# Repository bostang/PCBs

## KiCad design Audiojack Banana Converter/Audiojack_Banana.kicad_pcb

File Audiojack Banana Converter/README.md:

# Audiojack-Banana Converter

Converter audijoack 3.5mm <-> Banana Connector untuk keperluan pengujian _amplifier_ dengan input audio untuk tugas besar EL2205 Praktikum Elektronika 2024.

# Skematik

# Tampilan

## Tampak Atas

## Tampak Bawah

## Bird-view

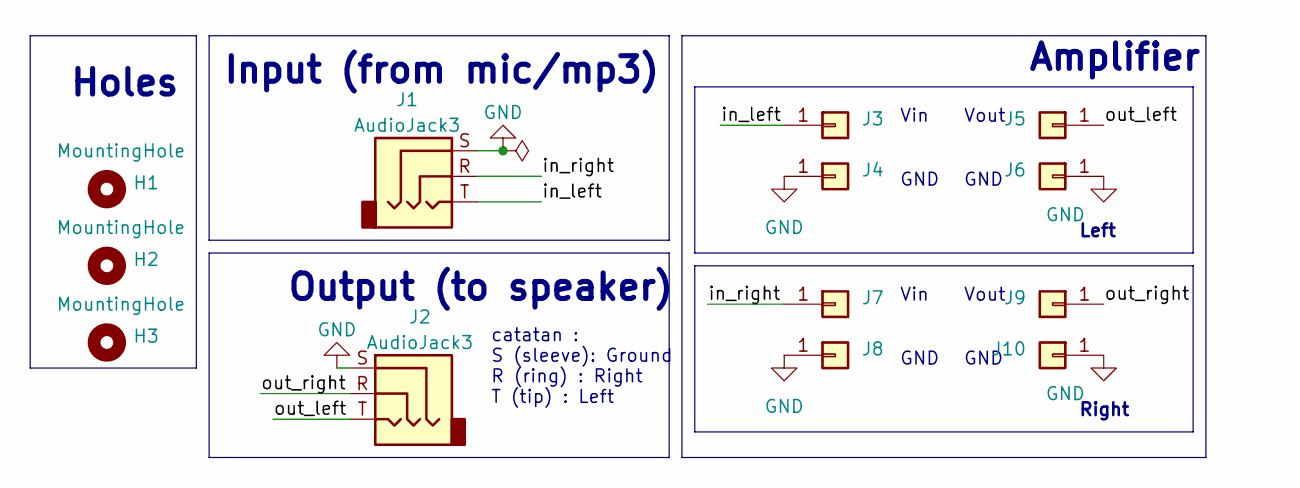
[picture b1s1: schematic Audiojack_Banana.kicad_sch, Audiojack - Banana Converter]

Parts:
H1, H2, H3: MountingHole; MountingHole_3.2mm_M3
J1, J2: AudioJack3; Jack_3.5mm_CUI_SJ-3523-SMT_Horizontal
J3, J4, J5, J6, J7, J8, J9, J10: Conn_01x01; Banana_Jack_1Pin

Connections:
/in_left: J1.T, J3.1
/in_right: J1.R, J7.1
/out_left: J2.T, J5.1
/out_right: J2.R, J9.1
GND: J1.S, J2.S, J4.1, J6.1, J8.1, J10.1

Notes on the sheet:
Amplifier
Vin
Vout
catatan : S (sleeve): Ground R (ring) : Right T (tip) : Left
Input (from mic/mp3)
GND
Left
Output (to speaker)
Right
Holes

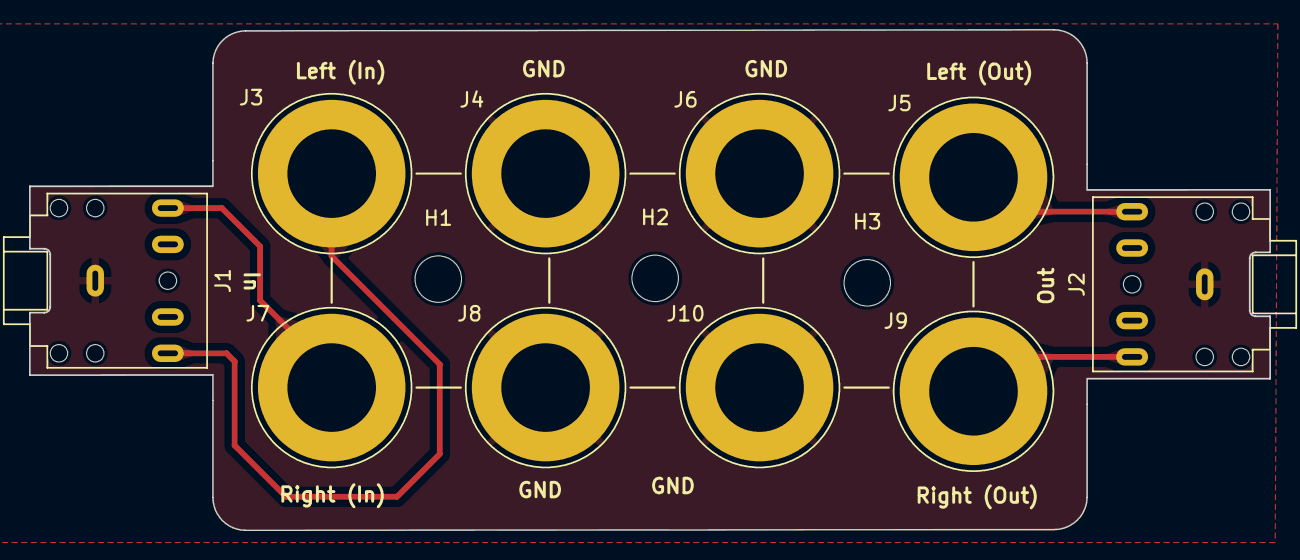
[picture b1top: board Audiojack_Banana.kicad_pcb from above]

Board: 2 copper layers, 85.4 x 34.5 mm, 13 parts (0 on the bottom side), 5 nets.

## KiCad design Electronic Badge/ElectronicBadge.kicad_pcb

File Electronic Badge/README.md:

# Electronic Badge

Lencana Elektronik yang berisi sebuah rangkaian sederhana : transistor sebagai switch sebagai tanda apresiasi bagi praktikan EL2205 Praktikum Elektronika 2024.

# Skematik

# Tampilan

## Tampak Atas

## Tampak Bawah

## Bird-view

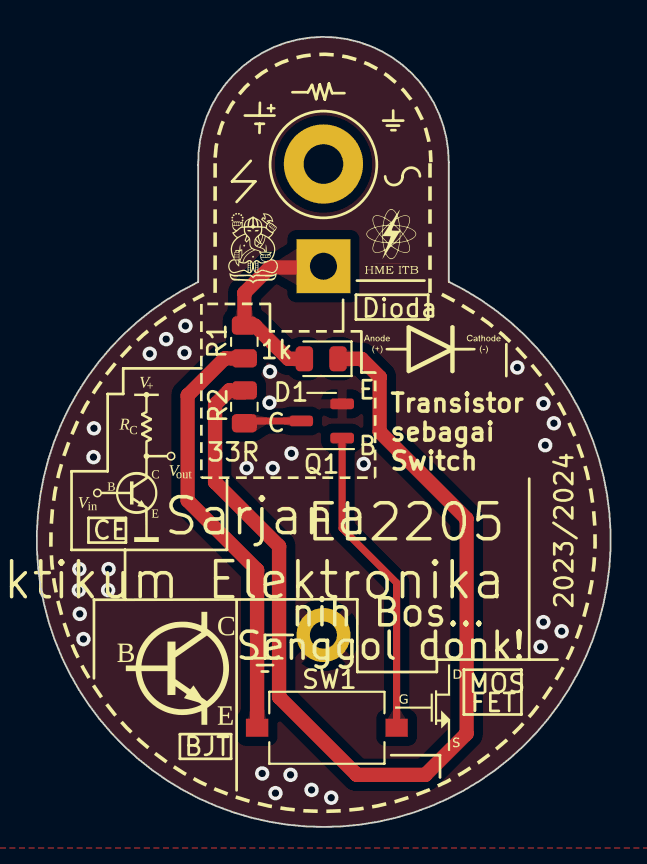
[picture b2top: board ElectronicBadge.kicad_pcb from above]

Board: 2 copper layers, 31.9 x 43.9 mm, 7 parts (1 on the bottom side), 6 nets.

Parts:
BT1: 3V; BatteryHolder_Keystone_107_1x23mm
D1: LED; LED_0805_2012Metric
H1: MountingHole; MountingHole_2.2mm_M2_Pad
Q1: NPN; SOT-23-3
R1: 1k; R_0805_2012Metric
R2: 33; R_0805_2012Metric
SW1: SW_SPST; SW_Tactile_SPST_NO_Straight_CK_PTS636Sx25SMTRLFS

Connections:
GND: BT1.2 (-), Q1.2 (E)
unnamed: D1.1 (K), R2.1
unnamed: Q1.1 (B), SW1.2 (B)
unnamed: Q1.3 (C), R2.2
unnamed: R1.2, SW1.1 (A)
VCC: BT1.1 (+), D1.2 (A), R1.1

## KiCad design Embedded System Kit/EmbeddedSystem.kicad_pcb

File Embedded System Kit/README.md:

# Embedded System Kit

Programmable ESP-32 development kit untuk tugas-tugas projek mata kuliah EL4121 Perancangan Sistem Embedded.

# Skematik

# Tampilan

## Tampak Atas

## Tampak Bawah

## Bird-view

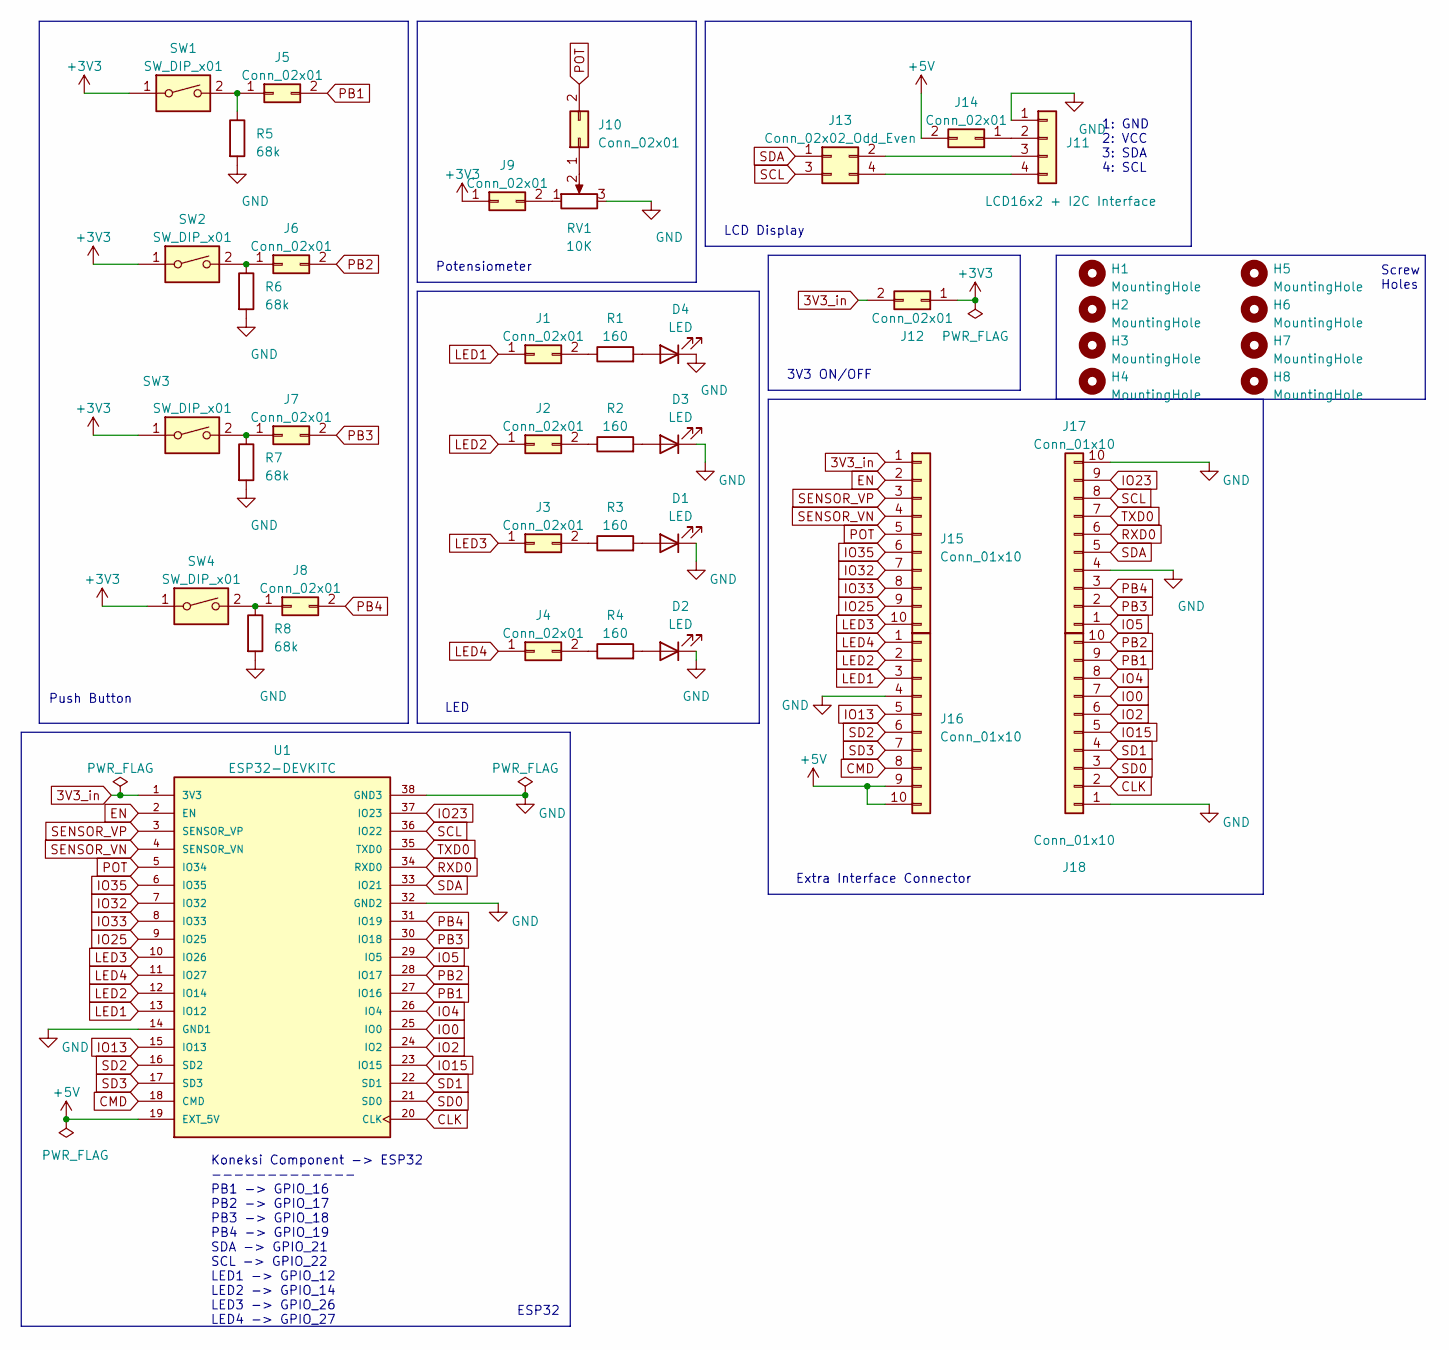
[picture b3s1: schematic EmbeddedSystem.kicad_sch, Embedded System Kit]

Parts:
D1, D2, D3, D4: LED; LED_0805_2012Metric
H1, H2, H3, H4, H5, H6, H7, H8: MountingHole; MountingHole_2.5mm
J1, J2, J3, J4, J5, J6, J7, J8, J9, J10, J12, J14: Conn_02x01; PinHeader_1x02_P2.54mm_Vertical
J11: LCD16x2 + I2C Interface; PinHeader_1x04_P2.54mm_Vertical
J13: Conn_02x02_Odd_Even; PinHeader_2x02_P2.54mm_Vertical
J15, J16, J17, J18: Conn_01x10; PinHeader_1x10_P2.54mm_Vertical
R1, R2, R3, R4: 160; R_0805_2012Metric
R5, R6, R7, R8: 68k; R_0805_2012Metric
RV1: 10K; Potentiometer_Alpha_RD901F-40-00D_Single_Vertical
SW1, SW2, SW3, SW4: SW_DIP_x01; SW_SPST_TL3342
U1: ESP32-DEVKITC; MODULE_ESP32-DEVKITC; PARTREV N/A

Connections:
3V3_in: J12.2, J15.1, U1.1 (3V3)
+3V3: J9.1, J12.1, SW1.1, SW2.1, SW3.1, SW4.1
+5V: J14.2, J16.9, J16.10, U1.19 (EXT_5V)
CLK: J18.2, U1.20 (CLK)
CMD: J16.8, U1.18 (CMD)
EN: J15.2, U1.2 (EN)
GND: D1.1 (K), D2.1 (K), D3.1 (K), D4.1 (K), J11.1, J16.4, J17.4, J17.10, J18.1, R5.2, R6.2, R7.2, R8.2, RV1.3, U1.14 (GND1), U1.32 (GND2), U1.38 (GND3)
IO0: J18.7, U1.25 (IO0)
IO2: J18.6, U1.24 (IO2)
IO4: J18.8, U1.26 (IO4)
IO5: J17.1, U1.29 (IO5)
IO13: J16.5, U1.15 (IO13)
IO15: J18.5, U1.23 (IO15)
IO23: J17.9, U1.37 (IO23)
IO25: J15.9, U1.9 (IO25)
IO32: J15.7, U1.7 (IO32)
IO33: J15.8, U1.8 (IO33)
IO35: J15.6, U1.6 (IO35)
LED1: J1.1, J16.3, U1.13 (IO12)
LED2: J2.1, J16.2, U1.12 (IO14)
LED3: J3.1, J15.10, U1.10 (IO26)
LED4: J4.1, J16.1, U1.11 (IO27)
unnamed: D1.2 (A), R3.2
unnamed: D2.2 (A), R4.2
unnamed: D3.2 (A), R2.2
unnamed: D4.2 (A), R1.2
unnamed: J1.2, R1.1
unnamed: J2.2, R2.1
unnamed: J3.2, R3.1
unnamed: J4.2, R4.1
unnamed: J5.1, R5.1, SW1.2
unnamed: J6.1, R6.1, SW2.2
unnamed: J7.1, R7.1, SW3.2
unnamed: J8.1, R8.1, SW4.2
unnamed: J9.2, RV1.1
unnamed: J10.1, RV1.2
unnamed: J11.2, J14.1
unnamed: J11.3, J13.2
unnamed: J11.4, J13.4
PB1: J5.2, J18.9, U1.27 (IO16)
PB2: J6.2, J18.10, U1.28 (IO17)
PB3: J7.2, J17.2, U1.30 (IO18)
PB4: J8.2, J17.3, U1.31 (IO19)
POT: J10.2, J15.5, U1.5 (IO34)
RXD0: J17.6, U1.34 (RXD0)
SCL: J13.3, J17.8, U1.36 (IO22)
SD0: J18.3, U1.21 (SD0)
SD1: J18.4, U1.22 (SD1)
SD2: J16.6, U1.16 (SD2)
SD3: J16.7, U1.17 (SD3)
SDA: J13.1, J17.5, U1.33 (IO21)
SENSOR_VN: J15.4, U1.4 (SENSOR_VN)
SENSOR_VP: J15.3, U1.3 (SENSOR_VP)
TXD0: J17.7, U1.35 (TXD0)

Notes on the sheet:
Extra Interface Connector
1: GND 2: VCC 3: SDA 4: SCL
ESP32
Potensiometer
LED
Screw Holes
Push Button
Koneksi Component -> ESP32 ------------- PB1 -> GPIO_16 PB2 -> GPIO_17 PB3 -> GPIO_18 PB4 -> GPIO_19 SDA -> GPIO_21 SCL -> GPIO_22 LED1 -> GPIO_12 LED2 -> GPIO_14 LED3 -> GPIO_26 LED4 -> GPIO_27
LCD Display
3V3 ON/OFF

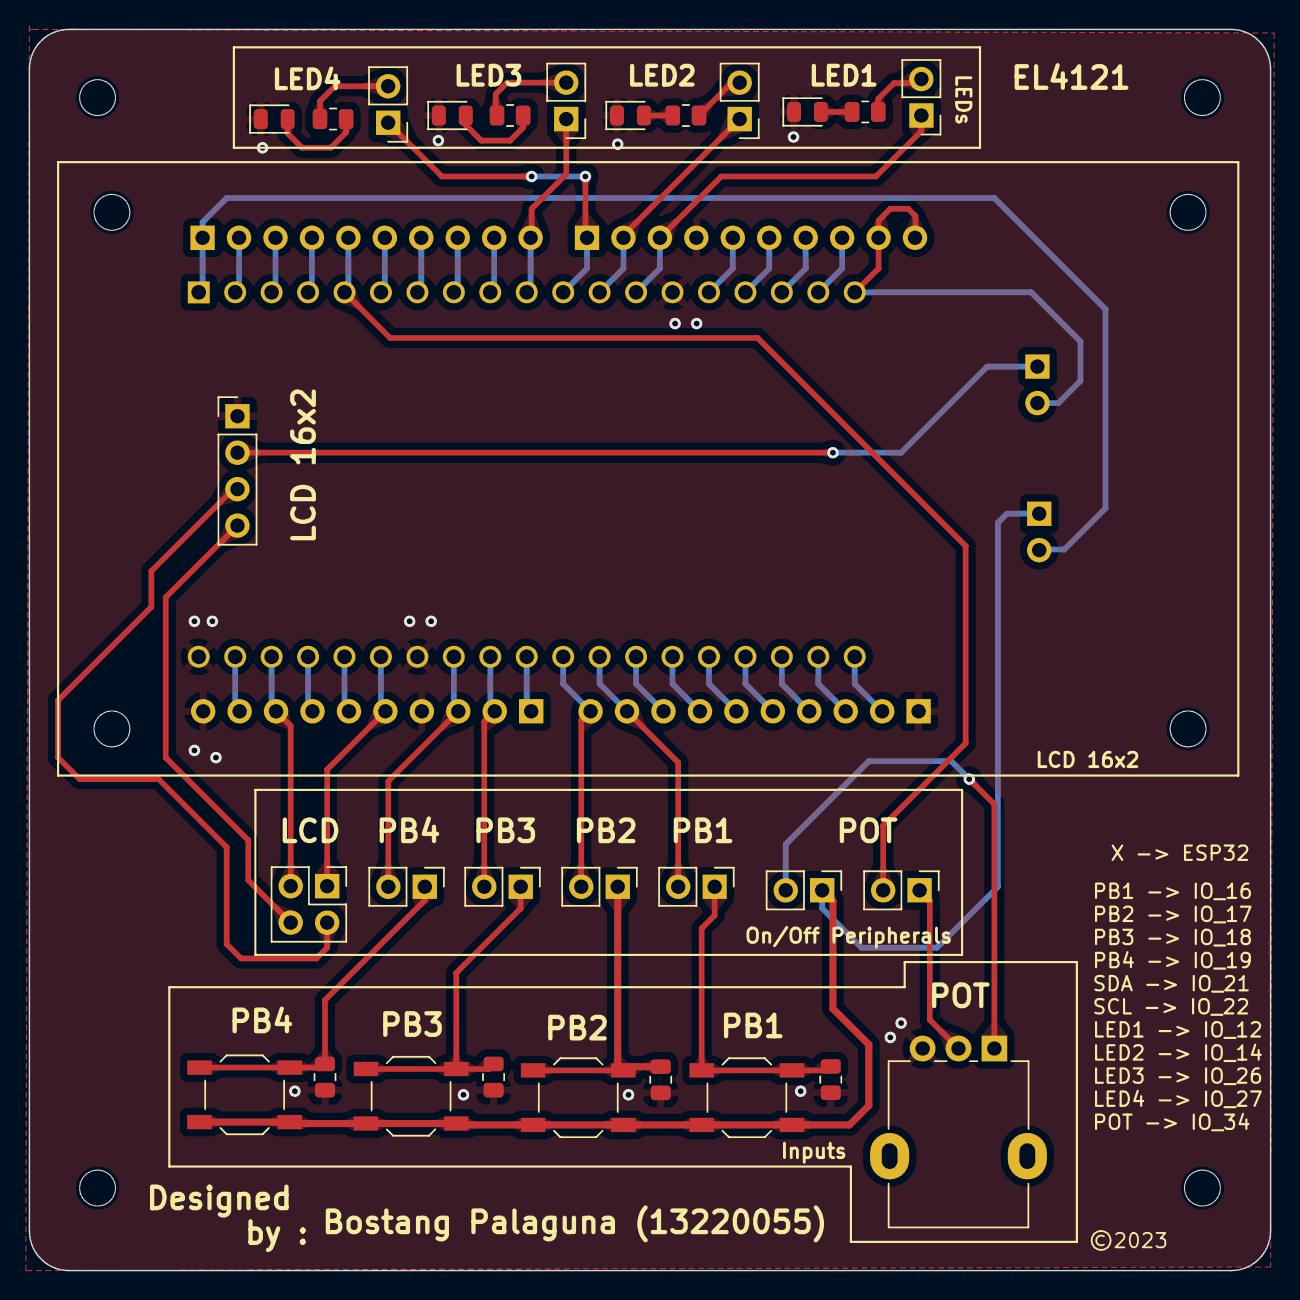
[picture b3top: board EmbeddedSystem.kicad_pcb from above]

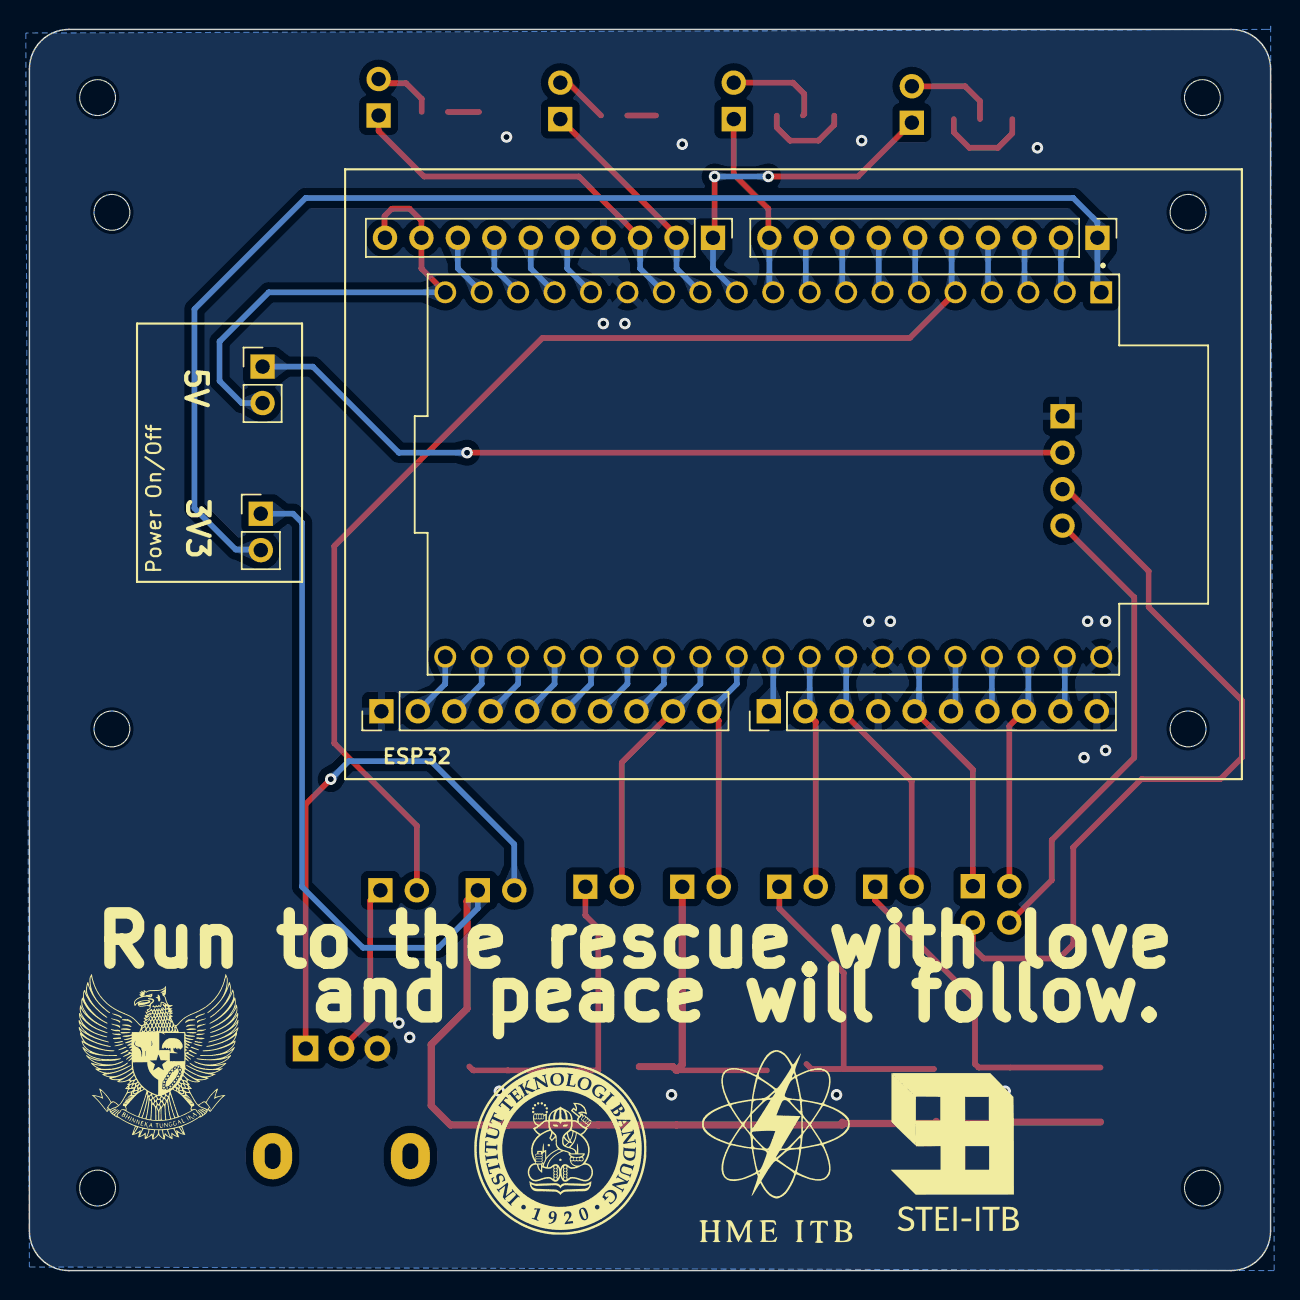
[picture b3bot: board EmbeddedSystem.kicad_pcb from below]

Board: 2 copper layers, 86.5 x 86.5 mm, 44 parts (7 on the bottom side), 54 nets.

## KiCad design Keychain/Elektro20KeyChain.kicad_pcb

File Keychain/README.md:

# Electronic KeyChain

Sebuah gantungan kunci dengan rangkaian empat LED sebagai tanda solidaritas Teknik Elektro ITB angkatan 2020.

# Skematik

# Tampilan

## Tampak Atas

## Tampak Bawah

## Bird-view

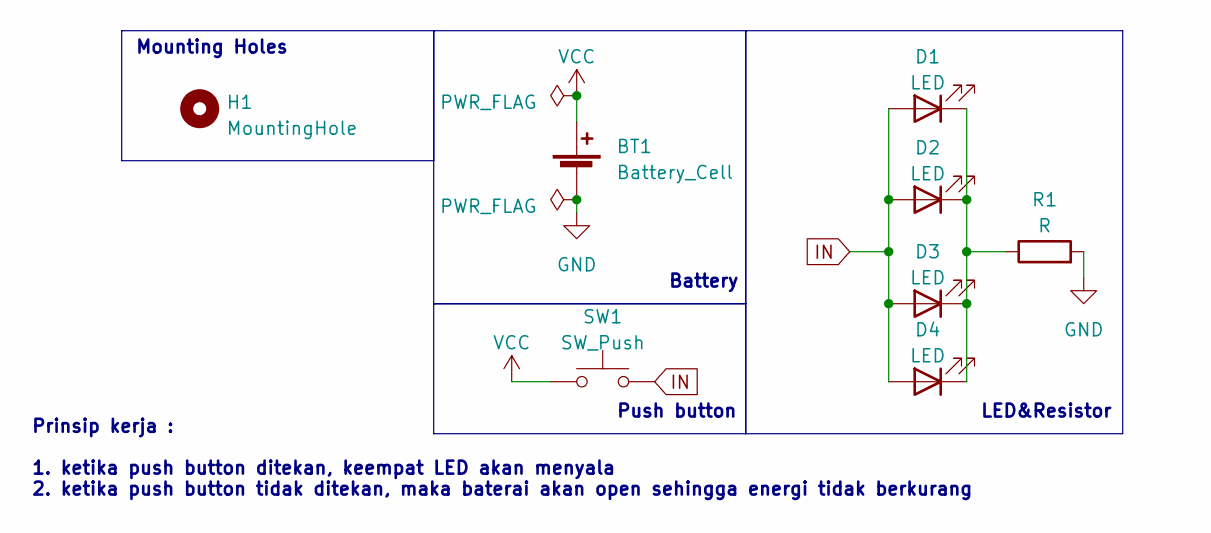
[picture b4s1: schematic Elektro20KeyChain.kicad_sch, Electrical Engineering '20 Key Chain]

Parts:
BT1: Battery_Cell; BatteryHolder_LINX_BAT-HLD-012-SMT
D1, D2, D3, D4: LED; LED_0603_1608Metric_Pad1.05x0.95mm_HandSolder
H1: MountingHole; MountingHole_2.1mm
R1: R; R_0603_1608Metric
SW1: SW_Push; SW_SPST_FSMSM

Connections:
GND: BT1.2 (-), R1.2
IN: D1.2 (A), D2.2 (A), D3.2 (A), D4.2 (A), SW1.2
unnamed: D1.1 (K), D2.1 (K), D3.1 (K), D4.1 (K), R1.1
VCC: BT1.1 (+), SW1.1

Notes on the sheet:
Battery
Push button
LED&Resistor
Prinsip kerja : 1. ketika push button ditekan, keempat LED akan menyala 2. ketika push button tidak ditekan, maka baterai akan open sehingga energi tidak berkurang
Mounting Holes

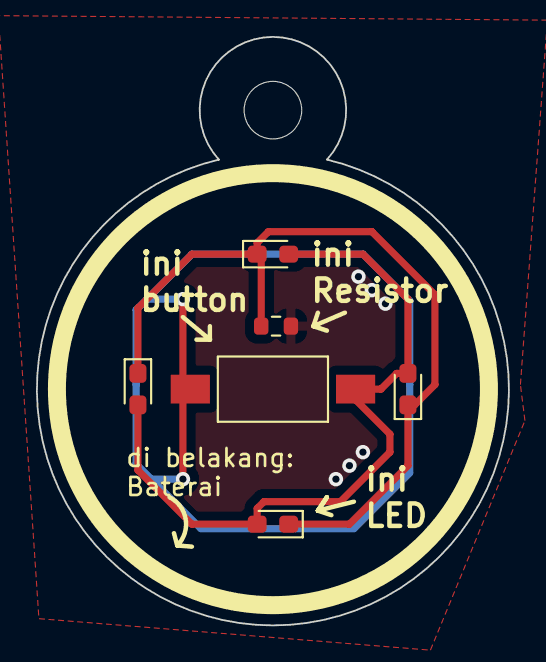
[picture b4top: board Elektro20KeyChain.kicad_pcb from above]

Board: 2 copper layers, 26.2 x 32.7 mm, 8 parts (1 on the bottom side), 4 nets.

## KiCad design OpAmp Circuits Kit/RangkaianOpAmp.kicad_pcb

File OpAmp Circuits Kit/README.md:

# Op Amp Circuits Kit

Kit Praktikum EL2101 Praktikum Rangkaian Elektrik Modul 3.

# Skematik

# Tampilan

## Tampak Atas

## Tampak Bawah

## Bird-view

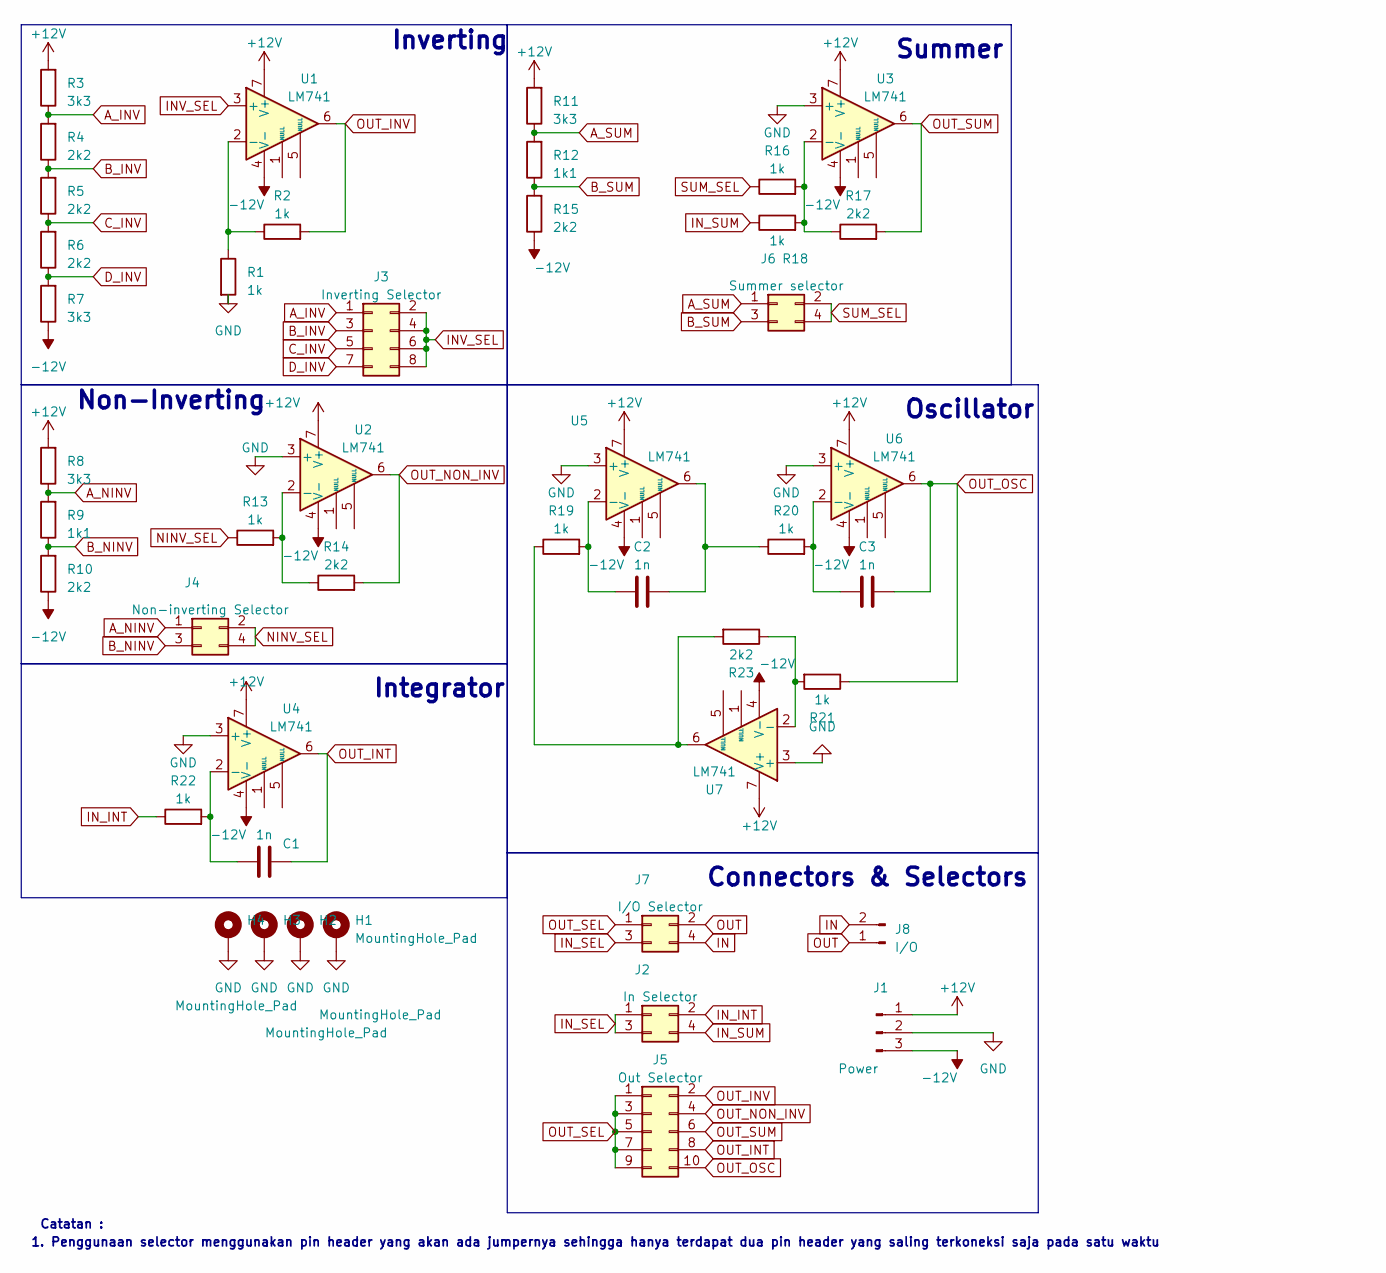
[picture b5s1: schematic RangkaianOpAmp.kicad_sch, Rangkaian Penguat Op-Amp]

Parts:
C1, C2, C3: 1n; C_0805_2012Metric
H1, H2, H3, H4: MountingHole_Pad; MountingHole_3.2mm_M3_DIN965_Pad
J1: Power; Banana_Jack_3Pin
J2: In Selector; PinHeader_2x02_P2.54mm_Vertical
J3: Inverting Selector; PinHeader_2x04_P2.54mm_Vertical
J4: Non-inverting Selector; PinHeader_2x02_P2.54mm_Vertical
J5: Out Selector; PinHeader_2x05_P2.54mm_Vertical
J6: Summer selector; PinHeader_2x02_P2.54mm_Vertical
J7: I/O Selector; PinHeader_2x02_P2.54mm_Vertical
J8: I/O; Banana_Jack_2Pin
R1, R2, R13, R16, R18, R19, R20, R21, R22: 1k; R_0805_2012Metric
R3, R7, R8, R11: 3k3; R_0805_2012Metric
R4, R5, R6, R10, R14, R15, R17, R23: 2k2; R_0805_2012Metric
R9, R12: 1k1; R_0805_2012Metric
U1, U2, U3, U4, U5, U6, U7: LM741; Fairchild_LSOP-8

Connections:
+12V: J1.1, R3.2, R8.2, R11.2, U1.7 (V+), U2.7 (V+), U3.7 (V+), U4.7 (V+), U5.7 (V+), U6.7 (V+), U7.7 (V+)
-12V: J1.3, R7.1, R10.1, R15.1, U1.4 (V-), U2.4 (V-), U3.4 (V-), U4.4 (V-), U5.4 (V-), U6.4 (V-), U7.4 (V-)
A_INV: J3.1, R3.1, R4.2
A_NINV: J4.1, R8.1, R9.2
A_SUM: J6.1, R11.1, R12.2
B_INV: J3.3, R4.1, R5.2
B_NINV: J4.3, R9.1, R10.2
B_SUM: J6.3, R12.1, R15.2
C_INV: J3.5, R5.1, R6.2
D_INV: J3.7, R6.1, R7.2
GND: H1.1, H2.1, H3.1, H4.1, J1.2, R1.2, U2.3 (+), U3.3 (+), U4.3 (+), U5.3 (+), U6.3 (+), U7.3 (+)
IN: J7.4, J8.2
INV_SEL: J3.2, J3.4, J3.6, J3.8, U1.3 (+)
IN_INT: J2.2, R22.1
IN_SEL: J2.1, J2.3, J7.3
IN_SUM: J2.4, R18.1
NINV_SEL: J4.2, J4.4, R13.1
unnamed: C2.2, R20.1, U5.6
unnamed: R19.1, R23.2, U7.6
unnamed: R1.1, R2.1, U1.2 (-)
unnamed: R13.2, R14.1, U2.2 (-)
unnamed: R16.2, R17.1, R18.2, U3.2 (-)
unnamed: C1.1, R22.2, U4.2 (-)
unnamed: C2.1, R19.2, U5.2 (-)
unnamed: C3.1, R20.2, U6.2 (-)
unnamed: R21.2, R23.1, U7.2 (-)
OUT: J7.2, J8.1
OUT_INT: C1.2, J5.8, U4.6
OUT_INV: J5.2, R2.2, U1.6
OUT_NON_INV: J5.4, R14.2, U2.6
OUT_OSC: C3.2, J5.10, R21.1, U6.6
OUT_SEL: J5.1, J5.3, J5.5, J5.7, J5.9, J7.1
OUT_SUM: J5.6, R17.2, U3.6
SUM_SEL: J6.2, J6.4, R16.1

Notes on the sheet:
Non-Inverting
Summer
Connectors & Selectors
Catatan :
1. Penggunaan selector menggunakan pin header yang akan ada jumpernya sehingga hanya terdapat dua pin header yang saling terkoneksi saja pada satu waktu
Inverting
Integrator
Oscillator

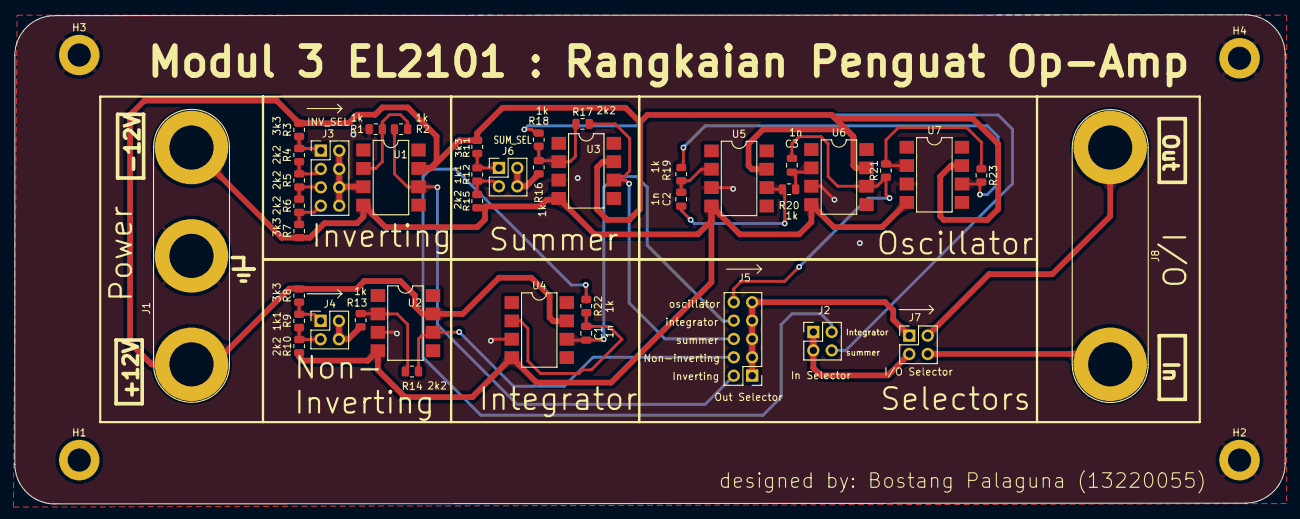
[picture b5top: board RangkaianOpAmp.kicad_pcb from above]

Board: 2 copper layers, 175.6 x 67.6 mm, 45 parts (0 on the bottom side), 34 nets.

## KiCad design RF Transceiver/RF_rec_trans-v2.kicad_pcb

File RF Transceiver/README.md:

# RF Transceiver

Radio-frequency Transmiter-Receiver menggunakan Arduino Nano, ESP32, dan modul NRF24L01.

# Skematik
## v2

## v1

# Tampilan

## Tampak Atas
## v2

## v1

## Tampak Bawah
## v2

## v1

## Bird-view
## v2

## v1

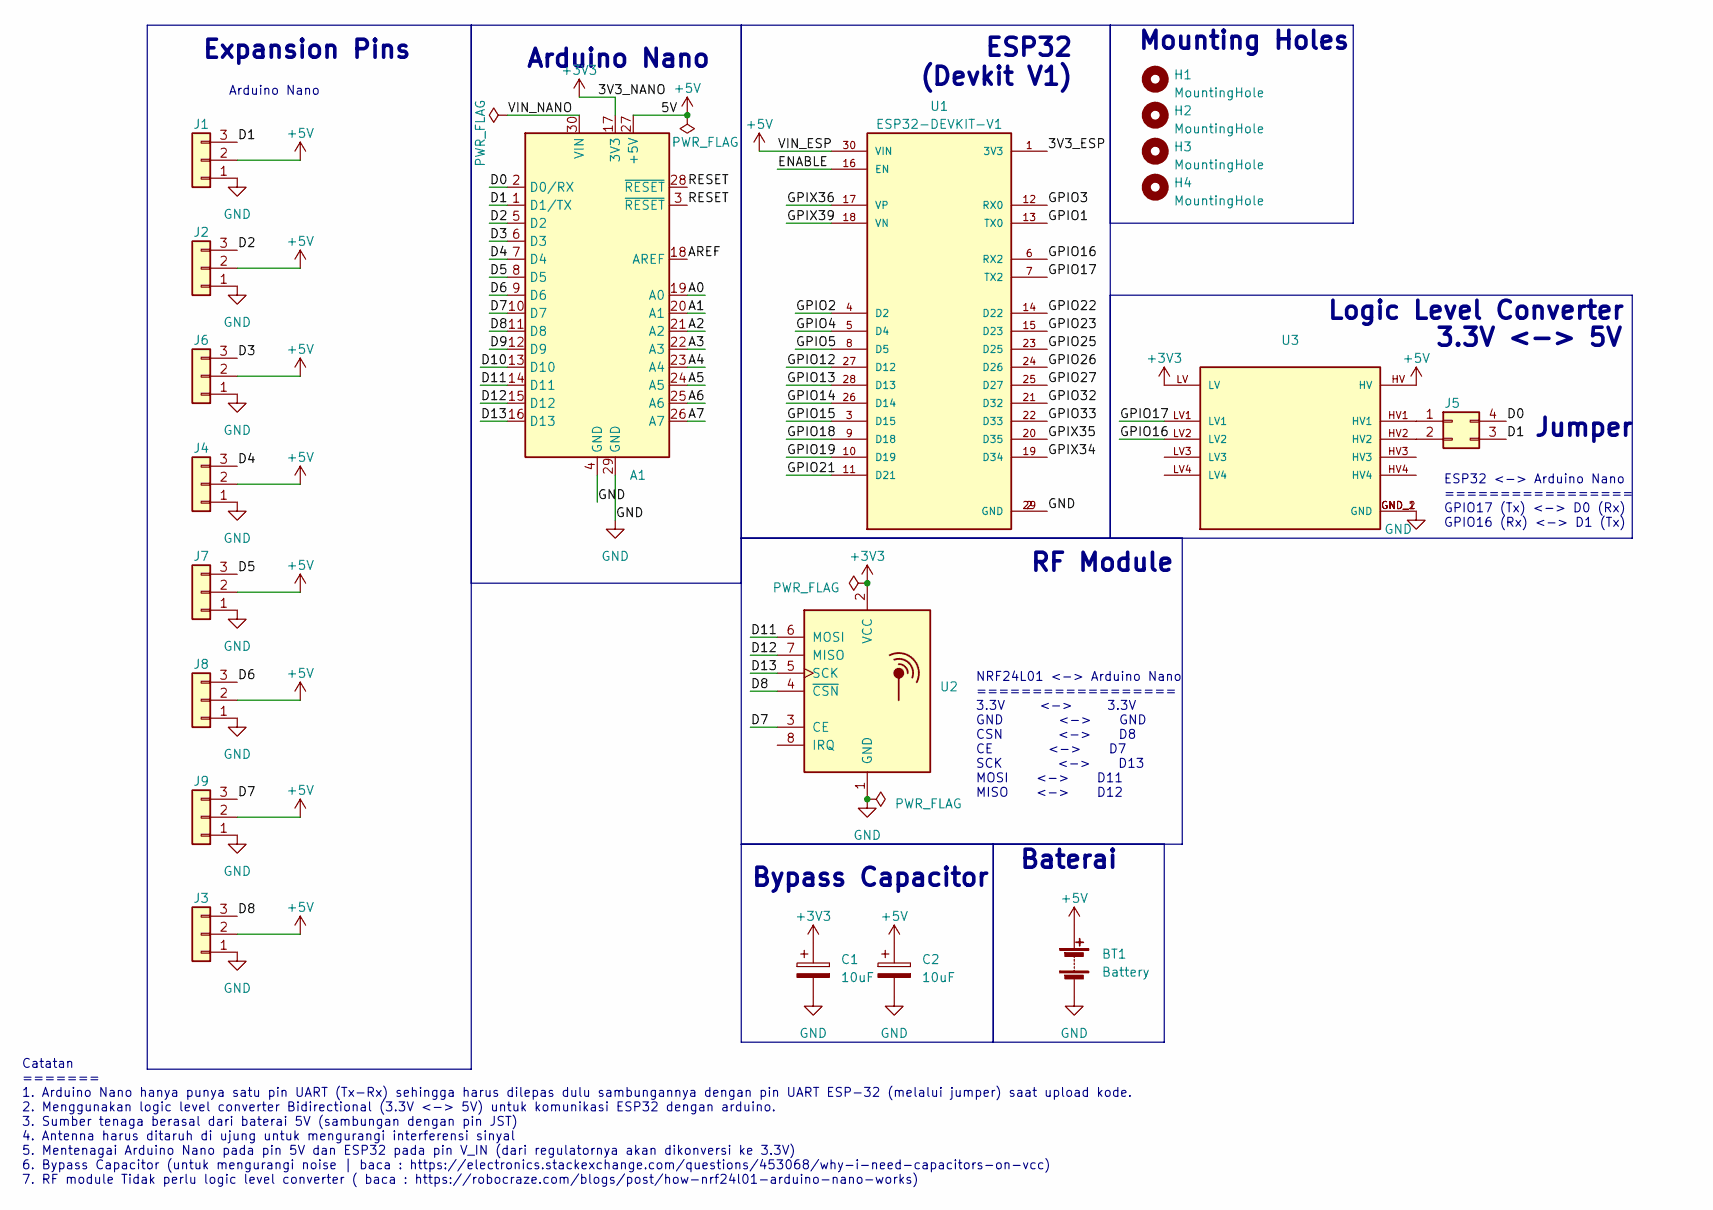
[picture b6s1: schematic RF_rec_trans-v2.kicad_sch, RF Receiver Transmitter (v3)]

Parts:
A1: Arduino_Nano_v3.x; Arduino_Nano_WithMountingHoles
BT1: Battery; JST_XH_S2B-XH-A-1_1x02_P2.50mm_Horizontal
C1, C2: 10uF; C_Radial_D5.0mm_H11.0mm_P2.00mm
H1, H2, H3, H4: MountingHole; MountingHole_2.2mm_M2
J1, J2, J3, J4, J6, J7, J8, J9: Conn_01x03; TerminalBlock_Phoenix_MKDS-3-3-5.08_1x03_P5.08mm_Horizontal
J5: Conn_02x02_Counter_Clockwise; PinHeader_2x02_P2.54mm_Vertical
U1: ESP32-DEVKIT-V1; MODULE_ESP32_DEVKIT_V1; PARTREV N/A
U2: NRF24L01_Breakout; NRF24L01+PA_LNA
U3: BOB-12009; Logic_Level_Converter; PARTREV 01

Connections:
+3V3: A1.17 (3V3), C1.1, U2.2 (VCC), U3.LV
+5V: A1.27 (+5V), BT1.1 (+), C2.1, J1.2, J2.2, J3.2, J4.2, J6.2, J7.2, J8.2, J9.2, U1.30 (VIN), U3.HV
/3V3_ESP: U1.1 (3V3)
/A0: A1.19 (A0)
/A1: A1.20 (A1)
/A2: A1.21 (A2)
/A3: A1.22 (A3)
/A4: A1.23 (A4)
/A5: A1.24 (A5)
/A6: A1.25 (A6)
/A7: A1.26 (A7)
/AREF: A1.18 (AREF)
/D0: A1.2 (D0/RX), J5.4
/D1: A1.1 (D1/TX), J1.3, J5.3
/D2: A1.5 (D2), J2.3
/D3: A1.6 (D3), J6.3
/D4: A1.7 (D4), J4.3
/D5: A1.8 (D5), J7.3
/D6: A1.9 (D6), J8.3
/D7: A1.10 (D7), J9.3, U2.3 (CE)
/D8: A1.11 (D8), J3.3, U2.4 (~CSN)
/D9: A1.12 (D9)
/D10: A1.13 (D10)
/D11: A1.14 (D11), U2.6 (MOSI)
/D12: A1.15 (D12), U2.7 (MISO)
/D13: A1.16 (D13), U2.5 (SCK)
/ENABLE: U1.16 (EN)
/GPIO1: U1.13 (TX0)
/GPIO2: U1.4 (D2)
/GPIO3: U1.12 (RX0)
/GPIO4: U1.5 (D4)
/GPIO5: U1.8 (D5)
/GPIO12: U1.27 (D12)
/GPIO13: U1.28 (D13)
/GPIO14: U1.26 (D14)
/GPIO15: U1.3 (D15)
/GPIO16: U1.6 (RX2), U3.LV2
/GPIO17: U1.7 (TX2), U3.LV1
/GPIO18: U1.9 (D18)
/GPIO19: U1.10 (D19)
/GPIO21: U1.11 (D21)
/GPIO22: U1.14 (D22)
/GPIO23: U1.15 (D23)
/GPIO25: U1.23 (D25)
/GPIO26: U1.24 (D26)
/GPIO27: U1.25 (D27)
/GPIO32: U1.21 (D32)
/GPIO33: U1.22 (D33)
/GPIX34: U1.19 (D34)
/GPIX35: U1.20 (D35)
/GPIX36: U1.17 (VP)
/GPIX39: U1.18 (VN)
/RESET: A1.3 (~RESET), A1.28 (~RESET)
/VIN_NANO: A1.30 (VIN)
GND: A1.4 (GND), A1.29 (GND), BT1.2 (-), C1.2, C2.2, J1.1, J2.1, J3.1, J4.1, J6.1, J7.1, J8.1, J9.1, U1.2 (GND), U1.29 (GND), U2.1 (GND), U3.GND_1 (GND), U3.GND_2 (GND)
unnamed: J5.1, U3.HV1
unnamed: J5.2, U3.HV2

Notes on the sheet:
Expansion Pins
Logic Level Converter
NRF24L01 <-> Arduino Nano ================== 3.3V <-> 3.3V GND <-> GND CSN <-> D8 CE <-> D7 SCK <-> D13 MOSI <-> D11 MISO <-> D12
Bypass Capacitor
ESP32 (Devkit V1)
RF Module
3.3V <-> 5V
ESP32 <-> Arduino Nano ================= GPIO17 (Tx) <-> D0 (Rx) GPIO16 (Rx) <-> D1 (Tx)
Jumper
Baterai
Catatan ======= 1. Arduino Nano hanya punya satu pin UART (Tx-Rx) sehingga harus dilepas dulu sambungannya dengan pin UART ESP-32 (melalui jumper) saat upload kode. 2. Menggunakan logic level converter Bidirectional (3.3V <-> 5V) untuk komunikasi ESP32 dengan arduino. 3. Sumber tenaga berasal dari 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
Arduino Nano
Mounting Holes

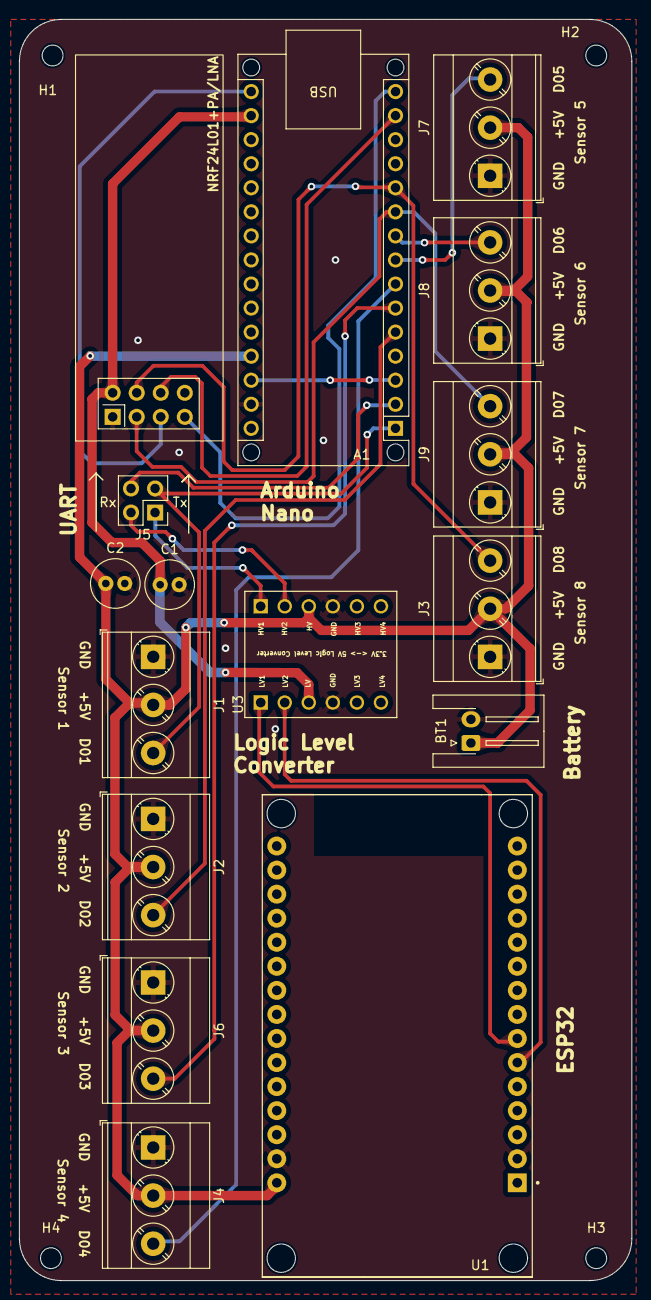
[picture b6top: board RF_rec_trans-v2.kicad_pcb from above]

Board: 2 copper layers, 64.7 x 133.2 mm, 20 parts (0 on the bottom side), 20 nets.

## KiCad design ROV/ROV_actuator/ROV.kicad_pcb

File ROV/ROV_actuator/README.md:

# ROV Controller

robot bawah air yang bergerak dengan dua buah motor 5V DC yang dikendalikan secara nirkabel dengan menggunakan modul NRF24L01

# Skematik

# Tampilan

## Tampak Atas

## Tampak Bawah

## Bird-view

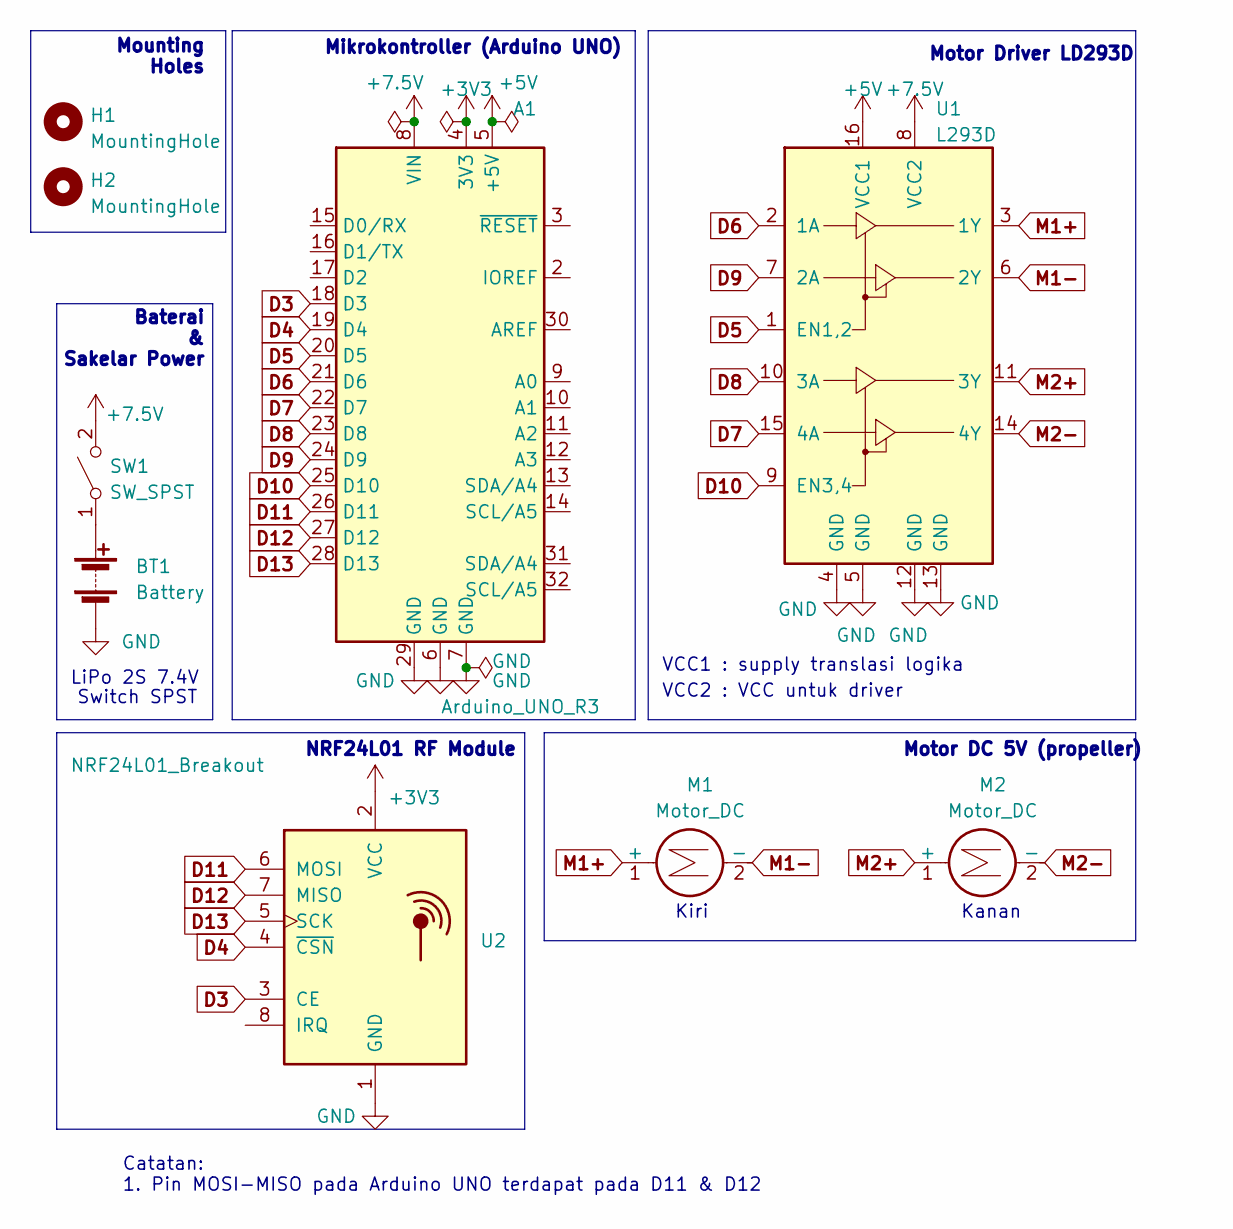
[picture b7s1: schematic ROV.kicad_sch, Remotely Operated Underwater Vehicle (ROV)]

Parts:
A1: Arduino_UNO_R3
BT1: Battery; Li-Po 2S
H1, H2: MountingHole; MountingHole_3.2mm_M3
M1, M2: Motor_DC; JST_XH_S2B-XH-A_1x02_P2.50mm_Horizontal
SW1: SW_SPST; JST_XH_S2B-XH-A_1x02_P2.50mm_Horizontal
U1: L293D; DIP-16_W7.62mm
U2: NRF24L01_Breakout; nRF24L01_Breakout

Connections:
+3V3: A1.4 (3V3), U2.2 (VCC)
+5V: A1.5 (+5V), U1.16 (VCC1)
+7.5V: A1.8 (VIN), SW1.2 (B), U1.8 (VCC2)
D3: A1.18 (D3), U2.3 (CE)
D4: A1.19 (D4), U2.4 (~CSN)
D5: A1.20 (D5), U1.1 (EN1,2)
D6: A1.21 (D6), U1.2 (1A)
D7: A1.22 (D7), U1.15 (4A)
D8: A1.23 (D8), U1.10 (3A)
D9: A1.24 (D9), U1.7 (2A)
D10: A1.25 (D10), U1.9 (EN3,4)
D11: A1.26 (D11), U2.6 (MOSI)
D12: A1.27 (D12), U2.7 (MISO)
D13: A1.28 (D13), U2.5 (SCK)
GND: A1.6 (GND), A1.7 (GND), A1.29 (GND), BT1.2 (-), U1.4 (GND), U1.5 (GND), U1.12 (GND), U1.13 (GND), U2.1 (GND)
M1+: M1.1 (+), U1.3 (1Y)
M1-: M1.2 (-), U1.6 (2Y)
M2+: M2.1 (+), U1.11 (3Y)
M2-: M2.2 (-), U1.14 (4Y)
unnamed: BT1.1 (+), SW1.1 (A)

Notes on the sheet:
Kiri
Catatan: 1. Pin MOSI-MISO pada Arduino UNO terdapat pada D11 & D12
LiPo 2S 7.4V
Mikrokontroller (Arduino UNO)
VCC1 : supply translasi logika
Kanan
NRF24L01 RF Module
Mounting Holes
VCC2 : VCC untuk driver
Switch SPST
Motor Driver LD293D
Motor DC 5V (propeller)
Baterai & Sakelar Power

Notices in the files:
Embedded System Kit/EmbeddedSystem.kicad_pcb:
©2023
